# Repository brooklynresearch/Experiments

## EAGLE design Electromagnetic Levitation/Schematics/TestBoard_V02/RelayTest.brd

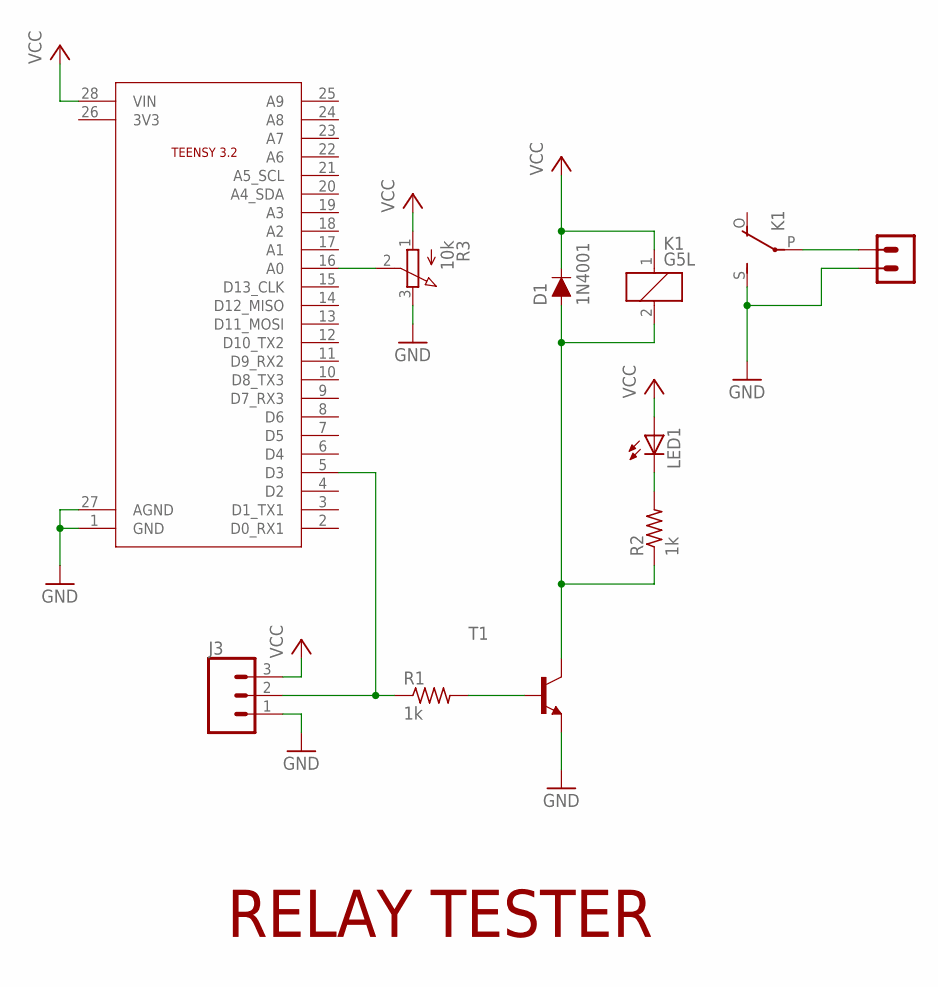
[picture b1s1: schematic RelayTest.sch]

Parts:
D1: 1N4001; DIODE-1N4001-KIT
J3: CONN_03SCREW; SCREWTERMINAL-3.5MM-3
K1: G5L; G5LE
LED1: LED3MM
R1, R2: 1k; 0204/7
R3: 10k; 3RP/1610N
T1: -NPN-TO92-EBC; TO92-EBC
U$1: TEENSY3.2; TEENSY
U$2: BIG_TERMINAL_2PINBIG; BIG_TERMINAL_2PIN

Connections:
GND: J3.1, K1.S, R3.3 (E), T1.E, U$1.1 (GND), U$1.27 (AGND), U$2.P$2
unnamed: LED1.K (C), R2.2
unnamed: R1.2, T1.B
unnamed: J3.2, R1.1, U$1.5 (D3)
unnamed: R3.2 (S), U$1.16 (A0)
unnamed: D1.A, K1.2, R2.1, T1.C
unnamed: K1.P, U$2.P$1
VCC: D1.C, J3.3, K1.1, LED1.A, R3.1 (A), U$1.28 (VIN)

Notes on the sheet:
RELAY TESTER

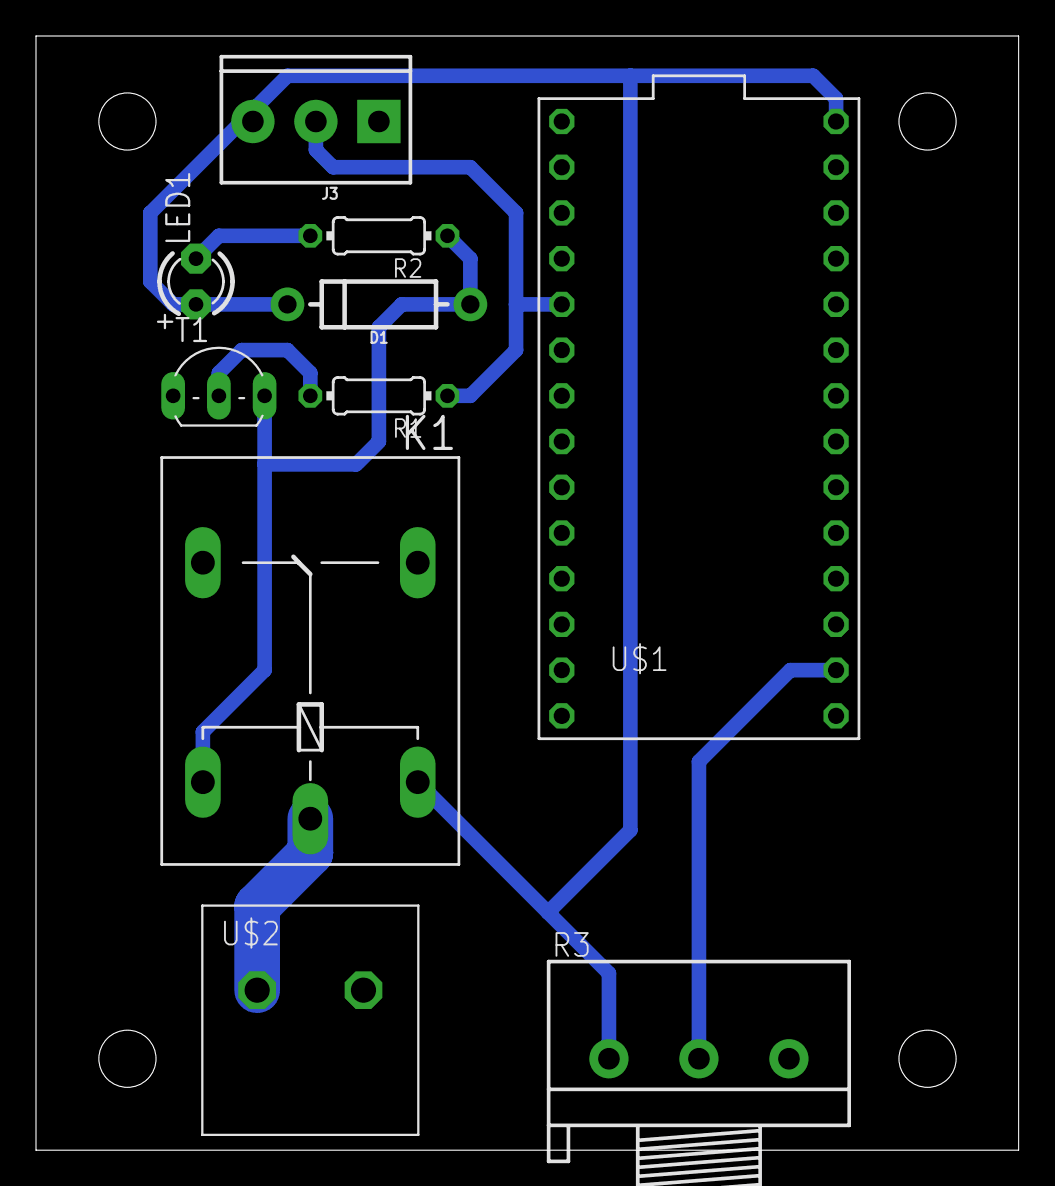
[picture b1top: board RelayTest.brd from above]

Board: 2 copper layers, 54.6 x 61.9 mm, 10 parts (0 on the bottom side), 8 nets.

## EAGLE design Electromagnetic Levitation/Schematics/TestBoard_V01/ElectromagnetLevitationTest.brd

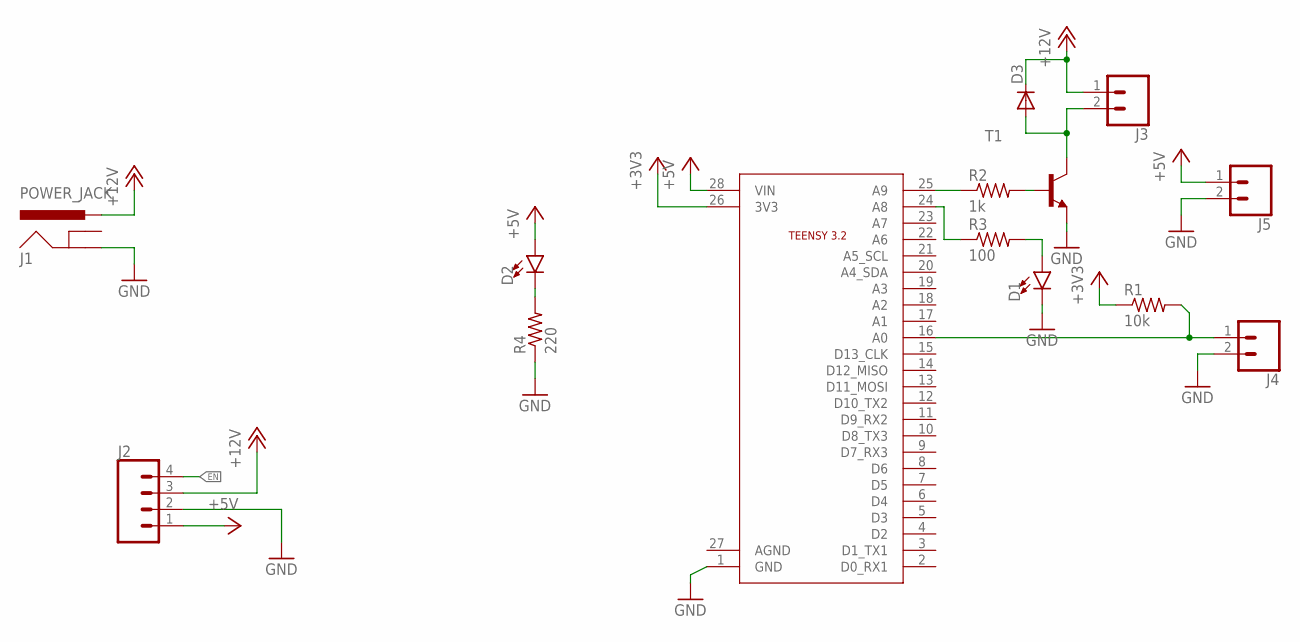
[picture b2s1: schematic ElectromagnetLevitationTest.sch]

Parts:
D1, D2: LED5MM; LED_5MM
D3: DIODE-D-7.5; D-7.5
J1: POWER_JACK; POWER_JACK_PTH
J2: CONN_04; 1X04
J3, J4, J5: CONN_023.5MM; SCREWTERMINAL-3.5MM-2
R1: 10k; 0204/7
R2: 1k; 0204/7
R3: 100; 0204/7
R4: 220; 0204/7
T1: -NPN-TO220V; TO220V
U$1: TEENSY3.2; TEENSY

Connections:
+3V3: R1.1, U$1.26 (3V3)
+5V: D2.A, J2.1, J5.1, U$1.28 (VIN)
+12V: D3.C, J1.PWR, J2.3, J3.1
EN: J2.4
GND: D1.K (C), J1.GND, J2.2, J4.2, J5.2, R4.1, T1.3 (E), U$1.1 (GND)
unnamed: J4.1, R1.2, U$1.16 (A0)
unnamed: R2.1, U$1.25 (A9)
unnamed: R2.2, T1.1 (B)
unnamed: D3.A, J3.2, T1.2 (C)
unnamed: R3.1, U$1.24 (A8)
unnamed: D1.A, R3.2
unnamed: D2.K (C), R4.2

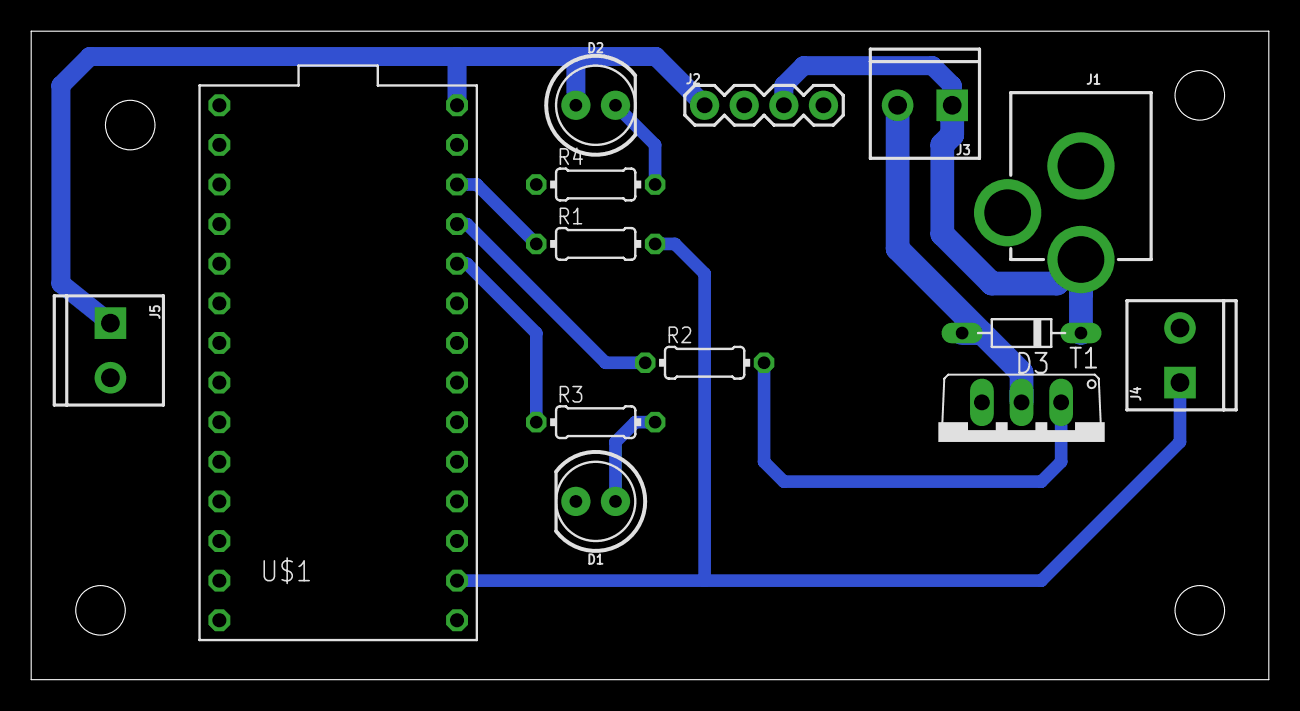
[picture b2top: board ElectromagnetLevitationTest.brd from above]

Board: 2 copper layers, 79.4 x 41.6 mm, 14 parts (0 on the bottom side), 11 nets.

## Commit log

2019-01-03 Initial Commit
    Electromagnetic Levitation Schematic, Code, and Documentation for the initial test.

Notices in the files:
parts and their libraries:
SparkFun-LED: Licensing: Creative Commons ShareAlike 4.0 International - https://creativecommons.org/licenses/by-sa/4.0
